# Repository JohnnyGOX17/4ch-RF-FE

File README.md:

# 4-Channel RF Front End

An open-source (KiCAD) RF front end with 4 independent RX &amp; TX channels optimized for MIMO/Radar prototyping. It implements an I2C bus for digital control of each channel’s attenuation and single-ended control of T/R switch for fast action. A switch-mode power supply and separate low dropout regulators for each channel are utilized to provide low-ripple power to RF Low Noise Amplifiers.

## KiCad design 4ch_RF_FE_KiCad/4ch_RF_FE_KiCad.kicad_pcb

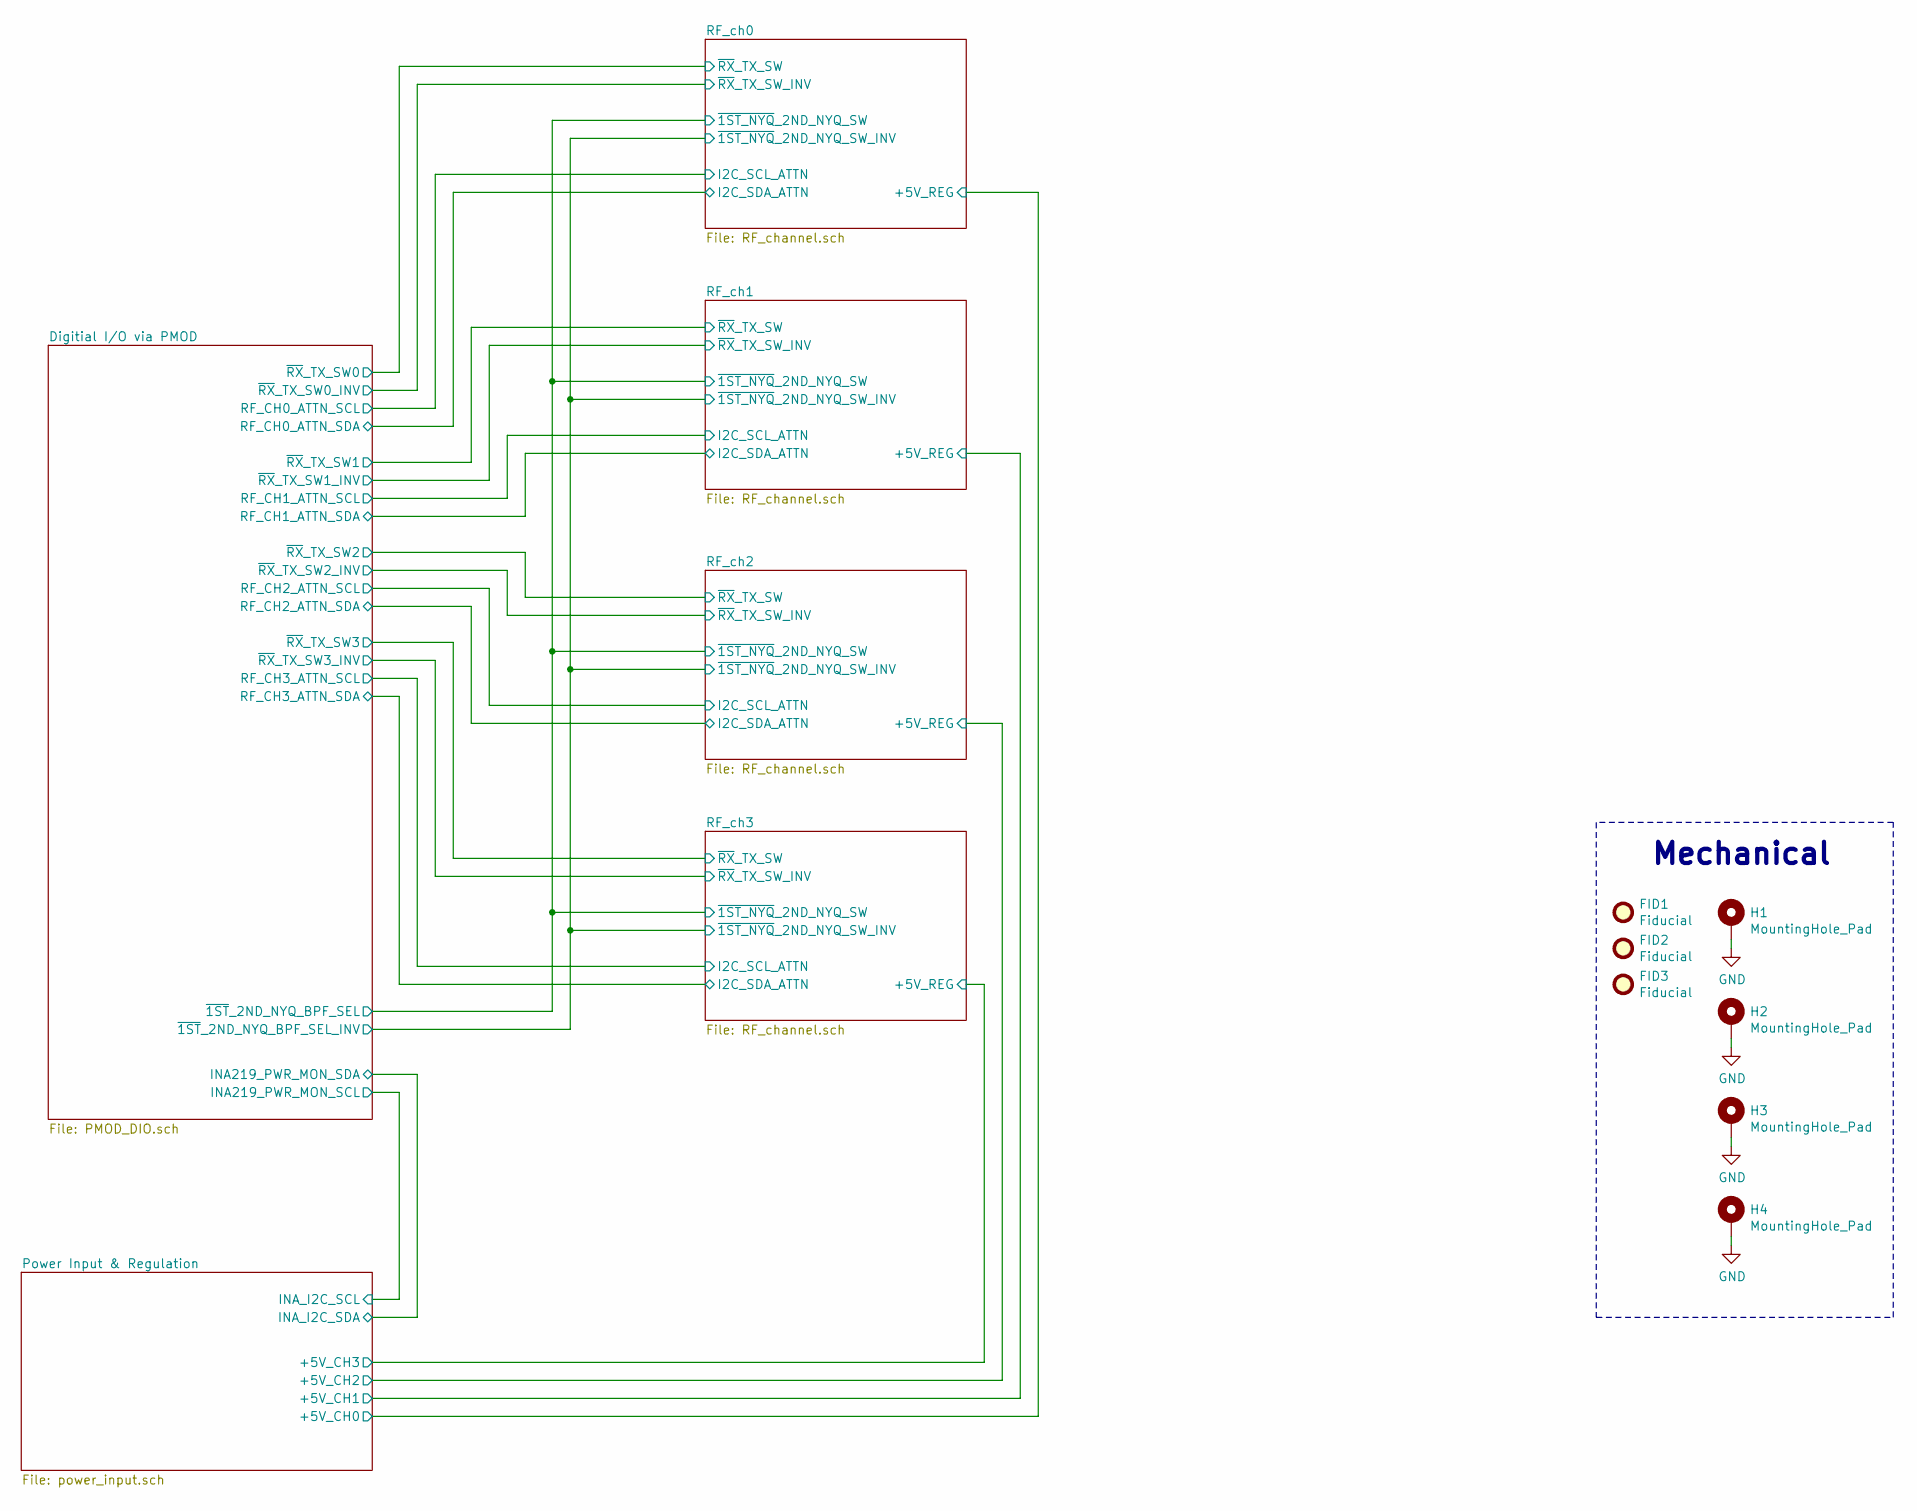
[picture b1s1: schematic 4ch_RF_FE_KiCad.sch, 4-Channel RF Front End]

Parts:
FID1, FID2, FID3: Fiducial; Fiducial_1mm_Mask2mm
H1, H2, H3, H4: MountingHole_Pad; MountingHole_3.7mm_Pad_Via

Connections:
GND: H1.1, H2.1, H3.1, H4.1; also elsewhere on the board

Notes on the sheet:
Mechanical

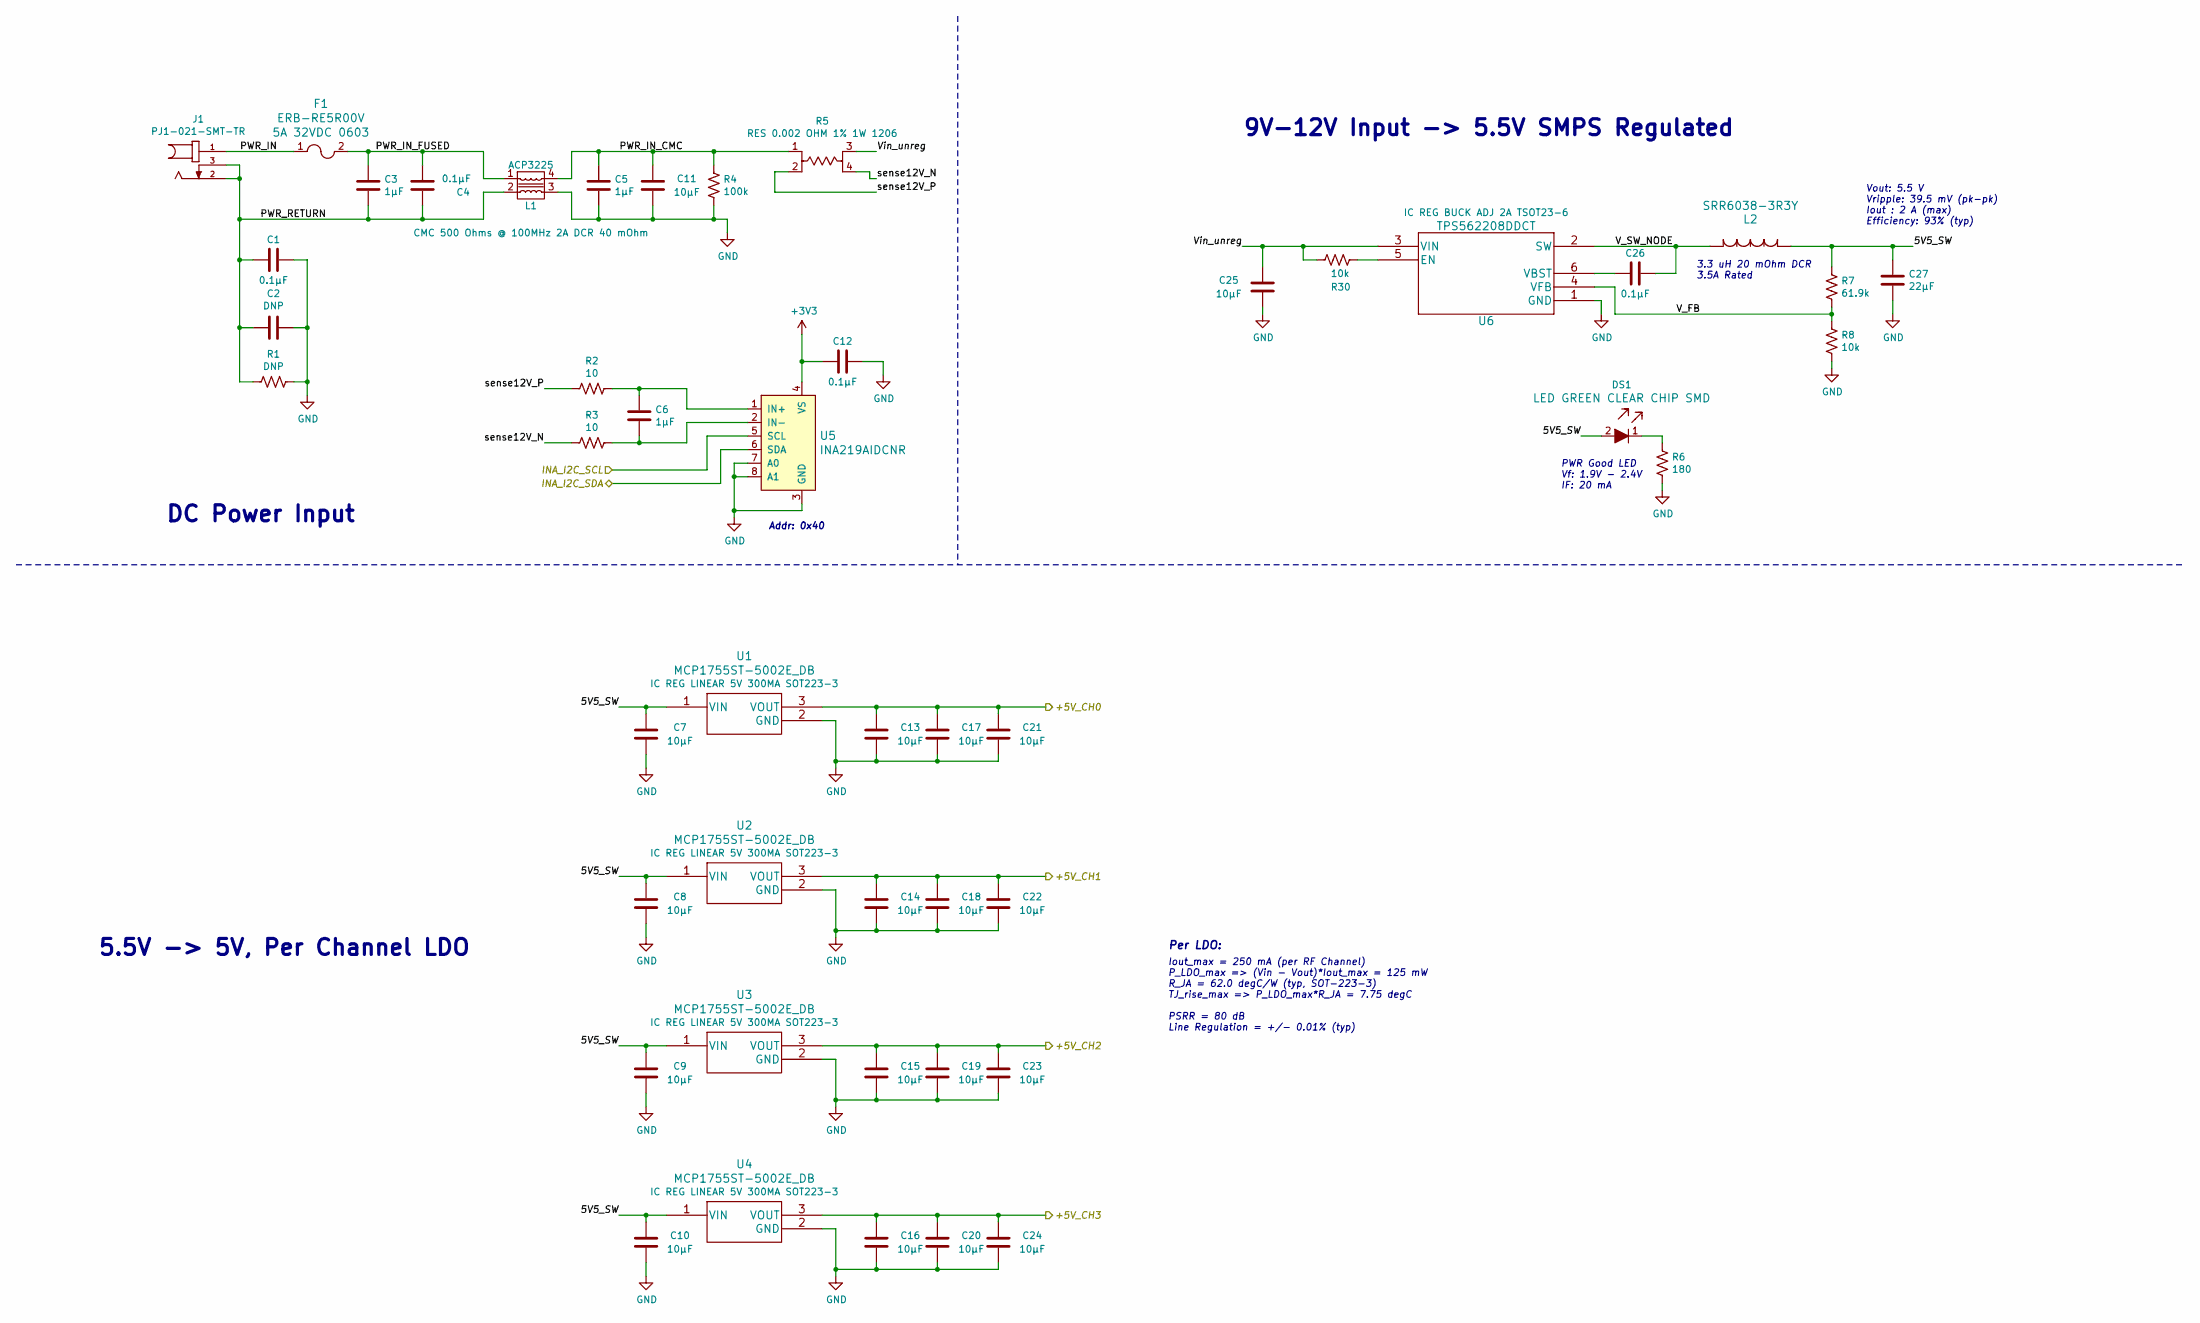
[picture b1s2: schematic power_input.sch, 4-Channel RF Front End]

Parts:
C1, C4, C12, C26: 0.1µF; C_0402_1005Metric; Digi-Key PN 490-13342-1-ND
C2: DNP; C_0402_1005Metric
C3, C5, C6: 1µF; C_0603_1608Metric_Pad1.05x0.95mm_HandSolder; Digi-Key PN 1276-1942-1-ND
C7, C8, C9, C10, C11, C13, C14, C15, C16, C17, C18, C19, C20, C21, C22, C23, C24, C25: 10µF; C_1206_3216Metric_Pad1.42x1.75mm_HandSolder; Digi-Key PN 1276-1804-1-ND
C27: 22µF; C_1206_3216Metric_Pad1.42x1.75mm_HandSolder; Digi-Key PN 1276-3146-1-ND
DS1: LTST-C190KGKT; LED_0603; MPN LTST-C190KGKT; Digi-Key_PN 160-1435-1-ND
F1: ERB-RE5R00V; 0603; Digi-Key_PN P15125CT-ND
J1: PJ1-021-SMT-TR; CUI_PJ1-021-SMT-TR; Digi-Key PN CP1-021PJCT-ND
L1: ACP3225; CMC_3225_2x2_LGA; Digi-Key PN 445-172408-1-ND
L2: SRR6038-3R3Y; Digi-Key PN SRR6038-3R3YCT-ND
R1: DNP; R_0402_1005Metric
R2, R3: 10; R_0402_1005Metric; Digi-Key PN 311-10.0LRCT-ND
R4: 100k; R_0402_1005Metric; Digi-Key PN 311-100KLRCT-ND
R5: CSR1206-0R002F1; CSR_4pin_1206_3216Metric_Pad1.42x1.75mm_HandSolder; Digi-Key PN 696-1370-1-ND
R6: 180; R_0603_1608Metric_Pad1.05x0.95mm_HandSolder; Digi-Key PN 311-180GRCT-ND
R7: 61.9k; R_0402_1005Metric; Digi-Key PN 311-61.9KLRCT-ND
R8, R30: 10k; R_0402_1005Metric; Digi-Key PN 311-10.0KLRCT-ND
U1, U2, U3, U4: MCP1755ST-5002E_DB; Digi-Key PN MCP1755ST-5002E/DBCT-ND
U5: INA219AIDCNR; SOT-23-8; MPN INA219AIDCNR; Digi-Key_PN 296-23770-1-ND
U6: TPS562208DDCT; Digi-Key PN 296-43806-1-ND

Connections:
+3V3: C12.1, U5.4 (VS); also elsewhere on the board
/Digitial I/O via PMOD/INA219_PWR_MON_SCL: U5.5 (SCL); also elsewhere on the board
/Digitial I/O via PMOD/INA219_PWR_MON_SDA: U5.6 (SDA); also elsewhere on the board
/Power Input & Regulation/5V5_SW: C7.1, C8.1, C9.1, C10.1, C27.1, DS1.2, L2.1, R7.1, U1.1 (VIN), U2.1 (VIN), U3.1 (VIN), U4.1 (VIN)
/Power Input & Regulation/+5V_CH0: C13.1, C17.1, C21.1, U1.3 (VOUT); also elsewhere on the board
/Power Input & Regulation/+5V_CH1: C14.1, C18.1, C22.1, U2.3 (VOUT); also elsewhere on the board
/Power Input & Regulation/+5V_CH2: C15.1, C19.1, C23.1, U3.3 (VOUT); also elsewhere on the board
/Power Input & Regulation/+5V_CH3: C16.1, C20.1, C24.1, U4.3 (VOUT); also elsewhere on the board
/Power Input & Regulation/PWR_IN: F1.1, J1.1
/Power Input & Regulation/PWR_IN_CMC: C5.1, C11.1, L1.4, R4.1, R5.1
/Power Input & Regulation/PWR_IN_FUSED: C3.1, C4.2, F1.2, L1.1
/Power Input & Regulation/PWR_RETURN: C1.1, C2.2, C3.2, C4.1, J1.2, J1.3, L1.2, R1.2
/Power Input & Regulation/V_FB: R7.2, R8.1, U6.4 (VFB)
/Power Input & Regulation/V_SW_NODE: C26.2, L2.2, U6.2 (SW)
/Power Input & Regulation/Vin_unreg: C25.1, R5.3, R30.2, U6.3 (VIN)
/Power Input & Regulation/sense12V_N: R3.2, R5.4
/Power Input & Regulation/sense12V_P: R2.2, R5.2
GND: C1.2, C2.1, C5.2, C7.2, C8.2, C9.2, C10.2, C11.2, C12.2, C13.2, C14.2, C15.2, C16.2, C17.2, C18.2, C19.2, C20.2, C21.2, C22.2, C23.2, C24.2, C25.2, C27.2, L1.3, R1.1, R4.2, R6.2, R8.2, U1.2 (GND), U2.2 (GND), U3.2 (GND), U4.2 (GND), U5.3 (GND), U5.7 (A0), U5.8 (A1), U6.1 (GND); also elsewhere on the board
unnamed: C6.1, R2.1, U5.1 (IN+)
unnamed: C6.2, R3.1, U5.2 (IN-)
unnamed: C26.1, U6.6 (VBST)
unnamed: DS1.1, R6.1
unnamed: R30.1, U6.5 (EN)

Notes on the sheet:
Addr: 0x40
3.3 uH 20 mOhm DCR 3.5A Rated
9V-12V Input -> 5.5V SMPS Regulated
Vout: 5.5 V Vripple: 39.5 mV (pk-pk) Iout : 2 A (max) Efficiency: 93% (typ)
PWR Good LED Vf: 1.9V - 2.4V IF: 20 mA
Iout_max = 250 mA (per RF Channel) P_LDO_max => (Vin - Vout)*Iout_max = 125 mW R_JA = 62.0 degC/W (typ, SOT-223-3) TJ_rise_max => P_LDO_max*R_JA = 7.75 degC PSRR = 80 dB Line Regulation = +/- 0.01% (typ)
DC Power Input
5.5V -> 5V, Per Channel LDO
Per LDO:

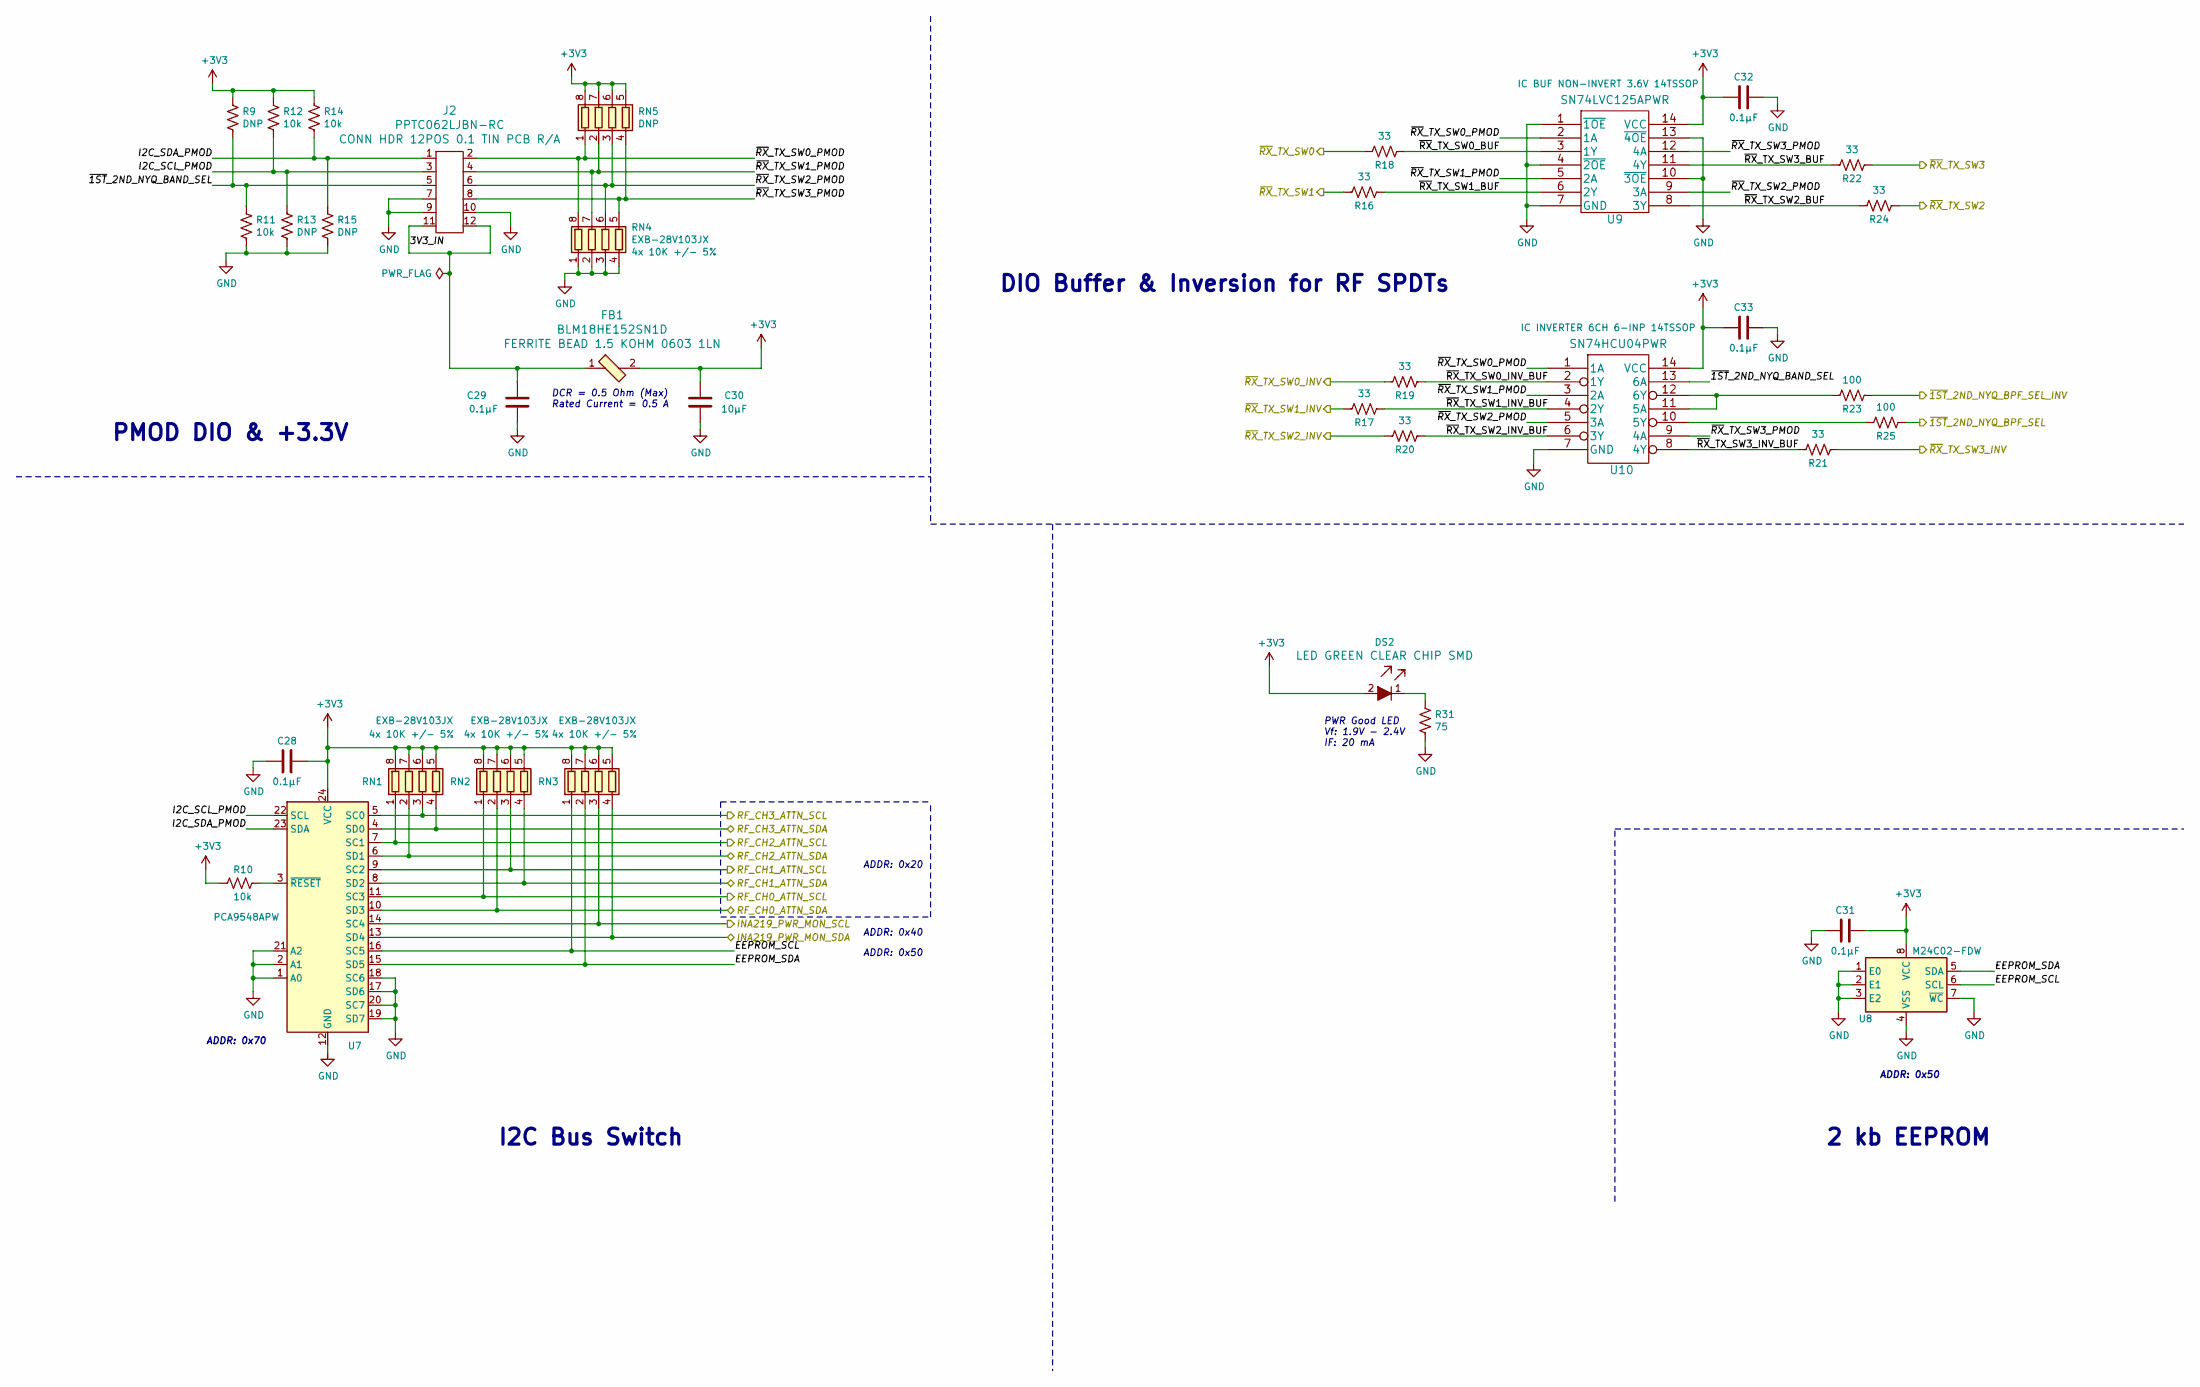
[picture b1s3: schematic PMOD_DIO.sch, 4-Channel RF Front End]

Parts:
C28, C29, C31, C32, C33: 0.1µF; C_0402_1005Metric; Digi-Key PN 490-13342-1-ND
C30: 10µF; C_1206_3216Metric_Pad1.42x1.75mm_HandSolder; Digi-Key PN 1276-1804-1-ND
DS2: LTST-C190KGKT; LED_0603; MPN LTST-C190KGKT; Digi-Key_PN 160-1435-1-ND
FB1: BLM18HE152SN1D; 0603; MPN BLM18HE152SN1D; Digi-Key_PN 490-5216-1-ND
J2: PPTC062LJBN-RC; PinHeader_2x06_P2.54mm_Horizontal; Digi-Key_PN S5520-ND
R9, R13, R15: DNP; R_0402_1005Metric
R10, R11, R12, R14: 10k; R_0402_1005Metric; Digi-Key PN 311-10.0KLRCT-ND
R16, R17, R18, R19, R20, R21, R22, R24: 33; R_0402_1005Metric; Digi-Key PN 311-33.0LRCT-ND
R23, R25: 100; R_0402_1005Metric; Digi-Key PN 311-100LRCT-ND
R31: 75; R_0603_1608Metric_Pad1.05x0.95mm_HandSolder; Digi-Key PN 311-75.0HRCT-ND
RN1, RN2, RN3, RN4: EXB-28V103JX; R_Array_Convex_4x0402; Digi-Key PN Y7103CT-ND
RN5: DNP; R_Array_Convex_4x0402
U7: PCA9548APW; TSSOP-24_4.4x7.8mm_P0.65mm
U8: M24C02-FDW; TSSOP-8_4.4x3mm_P0.65mm
U9: SN74LVC125APWR; Digi-Key PN 296-1222-1-ND
U10: SN74HCU04PWR; Digi-Key PN 296-9821-1-ND

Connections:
+3V3: C28.1, C30.1, C31.1, C32.2, C33.2, DS2.2, FB1.2, R9.1, R10.2, R12.1, R14.1, RN1.5 (R4.2), RN1.6 (R3.2), RN1.7 (R2.2), RN1.8 (R1.2), RN2.5 (R4.2), RN2.6 (R3.2), RN2.7 (R2.2), RN2.8 (R1.2), RN3.5 (R4.2), RN3.6 (R3.2), RN3.7 (R2.2), RN3.8 (R1.2), RN5.5 (R4.2), RN5.6 (R3.2), RN5.7 (R2.2), RN5.8 (R1.2), U7.24 (VCC), U8.8 (VCC), U9.14 (VCC), U10.14 (VCC); also elsewhere on the board
/Digitial I/O via PMOD/3V3_IN: C29.1, FB1.1, J2.11, J2.12
/Digitial I/O via PMOD/EEPROM_SCL: RN3.1 (R1.1), U7.16 (SC5), U8.6 (SCL)
/Digitial I/O via PMOD/EEPROM_SDA: RN3.2 (R2.1), U7.15 (SD5), U8.5 (SDA)
/Digitial I/O via PMOD/I2C_SCL_PMOD: J2.3, R12.2, R13.1, U7.22 (SCL)
/Digitial I/O via PMOD/I2C_SDA_PMOD: J2.1, R14.2, R15.1, U7.23 (SDA)
/Digitial I/O via PMOD/INA219_PWR_MON_SCL: RN3.3 (R3.1), U7.14 (SC4); also elsewhere on the board
/Digitial I/O via PMOD/INA219_PWR_MON_SDA: RN3.4 (R4.1), U7.13 (SD4); also elsewhere on the board
/Digitial I/O via PMOD/~1ST~_2ND_NYQ_BAND_SEL: J2.5, R9.2, R11.1, U10.13 (6A)
/Digitial I/O via PMOD/~RX~_TX_SW0_BUF: R18.1, U9.3 (1Y)
/Digitial I/O via PMOD/~RX~_TX_SW0_INV: R19.2; also elsewhere on the board
/Digitial I/O via PMOD/~RX~_TX_SW0_INV_BUF: R19.1, U10.2 (1Y)
/Digitial I/O via PMOD/~RX~_TX_SW0_PMOD: J2.2, RN4.8 (R1.2), RN5.1 (R1.1), U9.2 (1A), U10.1 (1A)
/Digitial I/O via PMOD/~RX~_TX_SW1_BUF: R16.1, U9.6 (2Y)
/Digitial I/O via PMOD/~RX~_TX_SW1_INV: R17.2; also elsewhere on the board
/Digitial I/O via PMOD/~RX~_TX_SW1_INV_BUF: R17.1, U10.4 (2Y)
/Digitial I/O via PMOD/~RX~_TX_SW1_PMOD: J2.4, RN4.7 (R2.2), RN5.2 (R2.1), U9.5 (2A), U10.3 (2A)
/Digitial I/O via PMOD/~RX~_TX_SW2_BUF: R24.2, U9.8 (3Y)
/Digitial I/O via PMOD/~RX~_TX_SW2_INV: R20.2; also elsewhere on the board
/Digitial I/O via PMOD/~RX~_TX_SW2_INV_BUF: R20.1, U10.6 (3Y)
/Digitial I/O via PMOD/~RX~_TX_SW2_PMOD: J2.6, RN4.6 (R3.2), RN5.3 (R3.1), U9.9 (3A), U10.5 (3A)
/Digitial I/O via PMOD/~RX~_TX_SW3_BUF: R22.2, U9.11 (4Y)
/Digitial I/O via PMOD/~RX~_TX_SW3_INV: R21.1; also elsewhere on the board
/Digitial I/O via PMOD/~RX~_TX_SW3_INV_BUF: R21.2, U10.8 (4Y)
/Digitial I/O via PMOD/~RX~_TX_SW3_PMOD: J2.8, RN4.5 (R4.2), RN5.4 (R4.1), U9.12 (4A), U10.9 (4A)
/RF_ch0/I2C_SCL_ATTN: RN2.1 (R1.1), U7.11 (SC3); also elsewhere on the board
/RF_ch0/I2C_SDA_ATTN: RN2.2 (R2.1), U7.10 (SD3); also elsewhere on the board
/RF_ch0/~1ST_NYQ~_2ND_NYQ_SW: R25.1; also elsewhere on the board
/RF_ch0/~1ST_NYQ~_2ND_NYQ_SW_INV: R23.1; also elsewhere on the board
/RF_ch0/~RX~_TX_SW: R18.2; also elsewhere on the board
/RF_ch1/I2C_SCL_ATTN: RN2.3 (R3.1), U7.9 (SC2); also elsewhere on the board
/RF_ch1/I2C_SDA_ATTN: RN2.4 (R4.1), U7.8 (SD2); also elsewhere on the board
/RF_ch1/~RX~_TX_SW: R16.2; also elsewhere on the board
/RF_ch2/I2C_SCL_ATTN: RN1.1 (R1.1), U7.7 (SC1); also elsewhere on the board
/RF_ch2/I2C_SDA_ATTN: RN1.2 (R2.1), U7.6 (SD1); also elsewhere on the board
/RF_ch2/~RX~_TX_SW: R24.1; also elsewhere on the board
/RF_ch3/I2C_SCL_ATTN: RN1.3 (R3.1), U7.5 (SC0); also elsewhere on the board
/RF_ch3/I2C_SDA_ATTN: RN1.4 (R4.1), U7.4 (SD0); also elsewhere on the board
/RF_ch3/~RX~_TX_SW: R22.1; also elsewhere on the board
GND: C28.2, C29.2, C30.2, C31.2, C32.1, C33.1, J2.7, J2.9, J2.10, R11.2, R13.2, R15.2, R31.2, RN4.1 (R1.1), RN4.2 (R2.1), RN4.3 (R3.1), RN4.4 (R4.1), U7.1 (A0), U7.2 (A1), U7.12 (GND), U7.17 (SD6), U7.18 (SC6), U7.19 (SD7), U7.20 (SC7), U7.21 (A2), U8.1 (E0), U8.2 (E1), U8.3 (E2), U8.4 (VSS), U8.7 (~WC), U9.1 (~1OE), U9.4 (~2OE), U9.7 (GND), U9.10 (~3OE), U9.13 (~4OE), U10.7 (GND); also elsewhere on the board
unnamed: DS2.1, R31.1
unnamed: R10.1, U7.3 (~RESET)
unnamed: R23.2, U10.11 (5A), U10.12 (6Y)
unnamed: R25.2, U10.10 (5Y)

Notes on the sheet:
DCR = 0.5 Ohm (Max) Rated Current = 0.5 A
PMOD DIO & +3.3V
ADDR: 0x20
ADDR: 0x40
ADDR: 0x50
2 kb EEPROM
ADDR: 0x70
DIO Buffer & Inversion for RF SPDTs
I2C Bus Switch
PWR Good LED Vf: 1.9V - 2.4V IF: 20 mA
